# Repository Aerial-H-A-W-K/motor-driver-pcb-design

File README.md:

# motor-driver-pcb-design
Eagle PCB Schematic and Design files for a board that routes power to 4 DRV8825 stepper motor drivers. The Step and Dir pins of the drivers are also routed to the digital pins of an Arduino Nano.

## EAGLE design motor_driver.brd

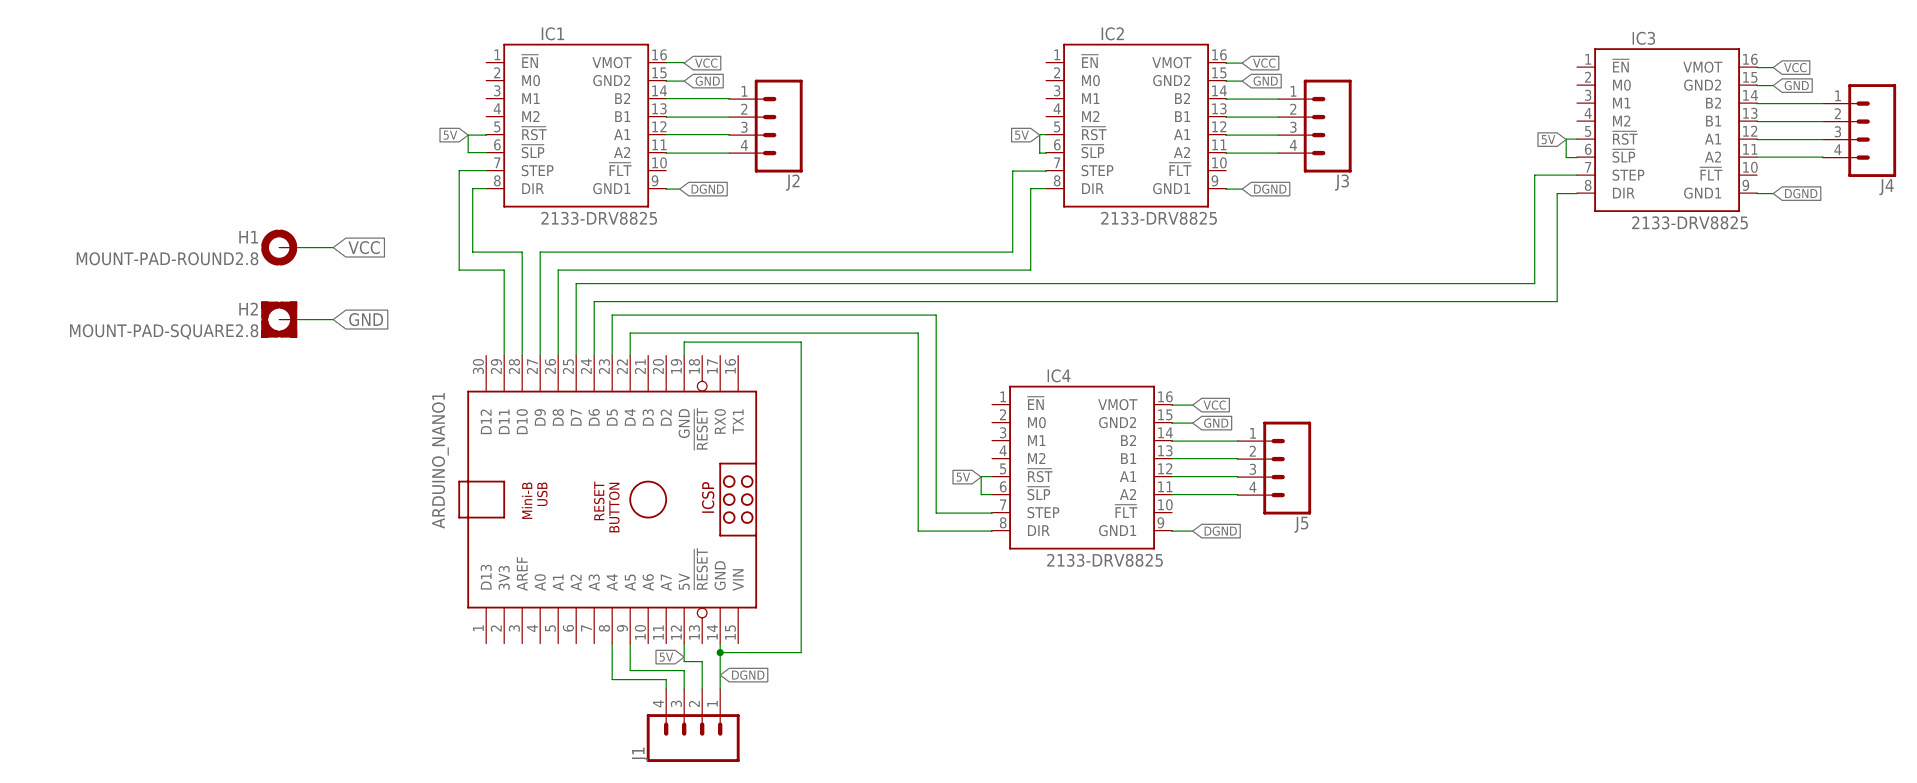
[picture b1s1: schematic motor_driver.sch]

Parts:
ARDUINO_NANO1: ARDUINO_NANO
H1: MOUNT-PAD-ROUND2.8; 2,8-PAD
H2: MOUNT-PAD-SQUARE2.8; 2,8-PAD-SQUARE
IC1, IC2, IC3, IC4: 2133-DRV8825; DRV8825
J1, J2, J3, J4, J5: CONN_04; 1X04

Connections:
5V: ARDUINO_NANO1.12 (5V), IC1.5 (!RST), IC1.6 (!SLP), IC2.5 (!RST), IC2.6 (!SLP), IC3.5 (!RST), IC3.6 (!SLP), IC4.5 (!RST), IC4.6 (!SLP), J1.2
DGND: ARDUINO_NANO1.14 (GND), ARDUINO_NANO1.19 (GND), IC1.9 (GND1), IC2.9 (GND1), IC3.9 (GND1), IC4.9 (GND1), J1.1
GND: H2.B2,8, IC1.15 (GND2), IC2.15 (GND2), IC3.15 (GND2), IC4.15 (GND2)
unnamed: ARDUINO_NANO1.29 (D11), IC1.7 (STEP)
unnamed: ARDUINO_NANO1.9 (A5), J1.3
unnamed: ARDUINO_NANO1.8 (A4), J1.4
unnamed: ARDUINO_NANO1.25 (D7), IC3.7 (STEP)
unnamed: ARDUINO_NANO1.26 (D8), IC2.8 (DIR)
unnamed: ARDUINO_NANO1.28 (D10), IC1.8 (DIR)
unnamed: ARDUINO_NANO1.23 (D5), IC4.7 (STEP)
unnamed: IC1.14 (B2), J2.1
unnamed: ARDUINO_NANO1.24 (D6), IC3.8 (DIR)
unnamed: IC1.13 (B1), J2.2
unnamed: IC1.12 (A1), J2.3
unnamed: ARDUINO_NANO1.27 (D9), IC2.7 (STEP)
unnamed: IC1.11 (A2), J2.4
unnamed: IC2.14 (B2), J3.1
unnamed: IC2.13 (B1), J3.2
unnamed: IC2.12 (A1), J3.3
unnamed: IC2.11 (A2), J3.4
unnamed: IC3.14 (B2), J4.1
unnamed: IC3.13 (B1), J4.2
unnamed: IC3.12 (A1), J4.3
unnamed: IC3.11 (A2), J4.4
unnamed: IC4.14 (B2), J5.1
unnamed: IC4.13 (B1), J5.2
unnamed: IC4.12 (A1), J5.3
unnamed: IC4.11 (A2), J5.4
unnamed: ARDUINO_NANO1.22 (D4), IC4.8 (DIR)
VCC: H1.B2,8, IC1.16 (VMOT), IC2.16 (VMOT), IC3.16 (VMOT), IC4.16 (VMOT)
VIN: ARDUINO_NANO1.15 (VIN)

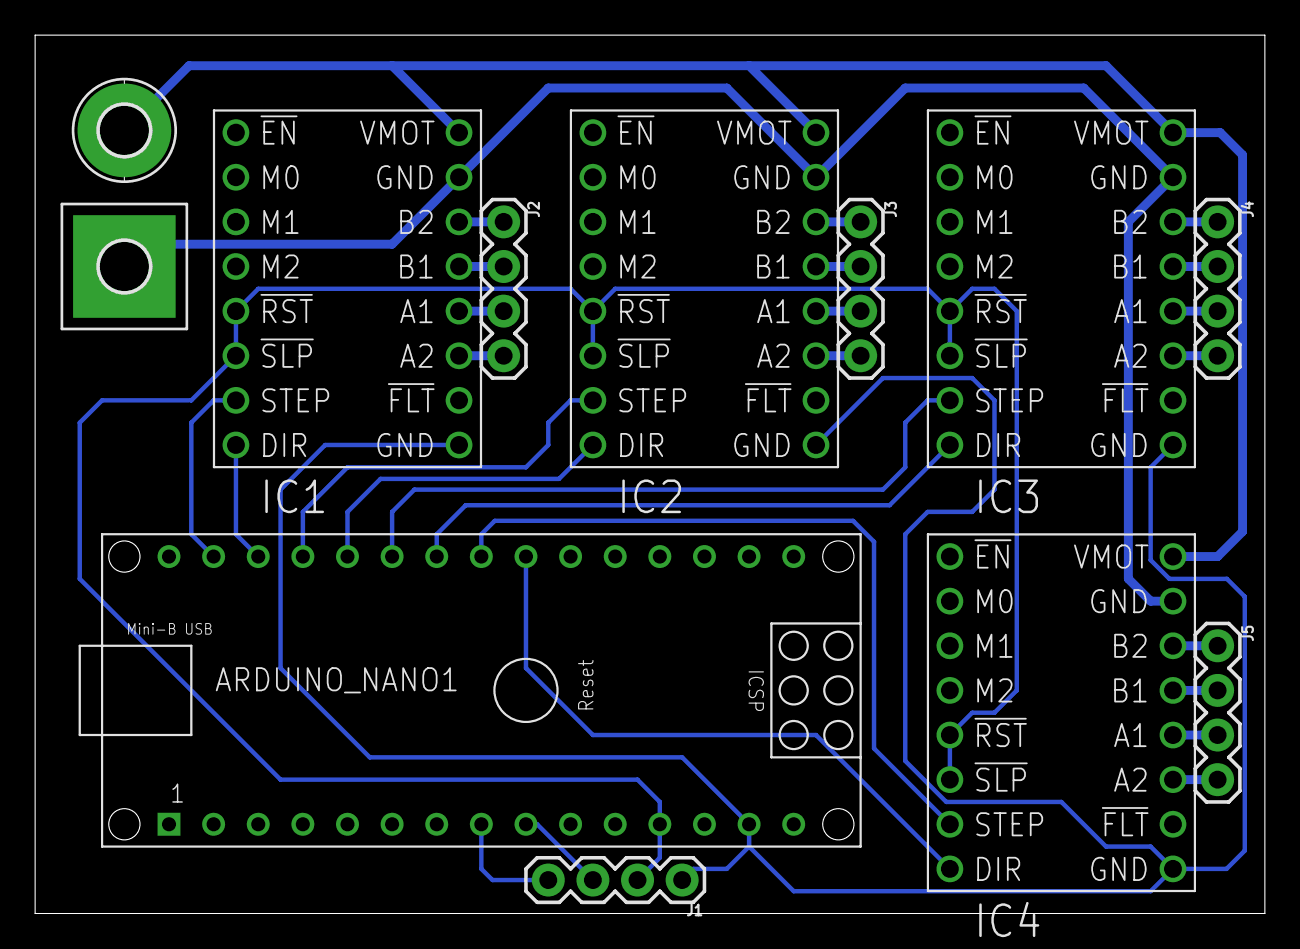
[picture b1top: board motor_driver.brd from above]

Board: 2 copper layers, 70.0 x 50.0 mm, 12 parts (0 on the bottom side), 30 nets.

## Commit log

2020-08-16 Added pcb design files and gerber outputs
2020-08-16 Removed ..gitignore.un~

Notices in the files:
parts and their libraries:
SparkFun-Connectors: Licensing: Creative Commons ShareAlike 4.0 International - https://creativecommons.org/licenses/by-sa/4.0
